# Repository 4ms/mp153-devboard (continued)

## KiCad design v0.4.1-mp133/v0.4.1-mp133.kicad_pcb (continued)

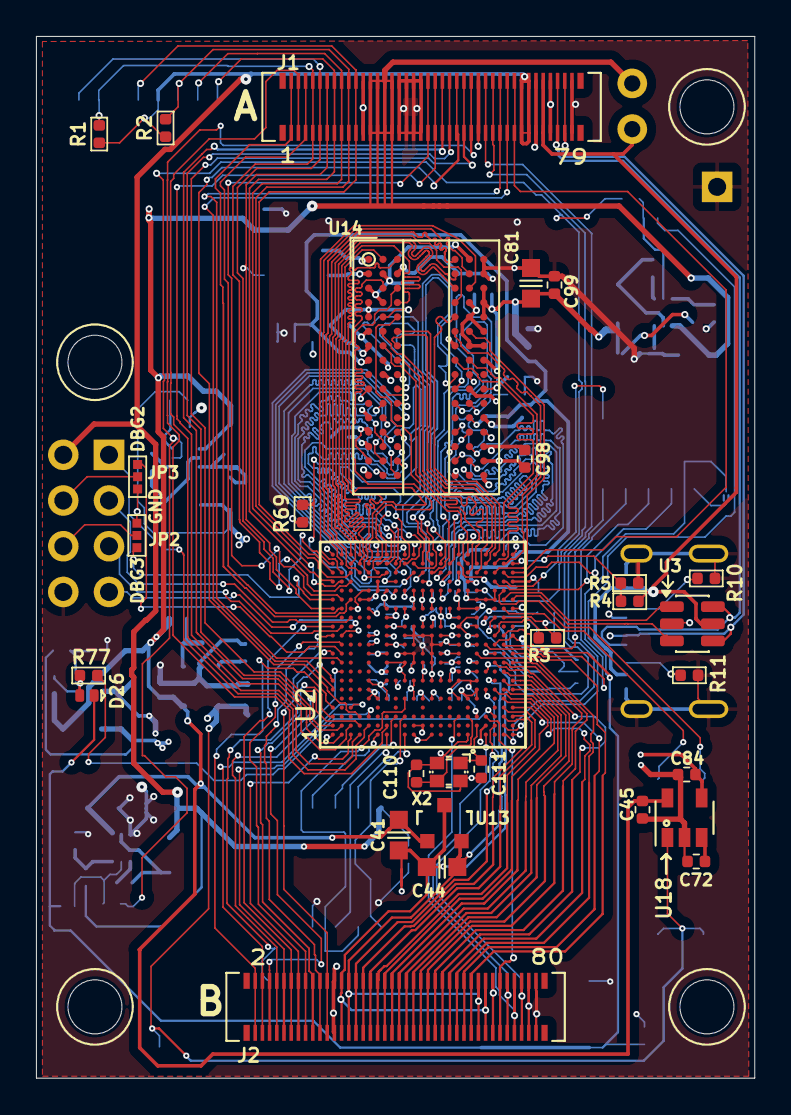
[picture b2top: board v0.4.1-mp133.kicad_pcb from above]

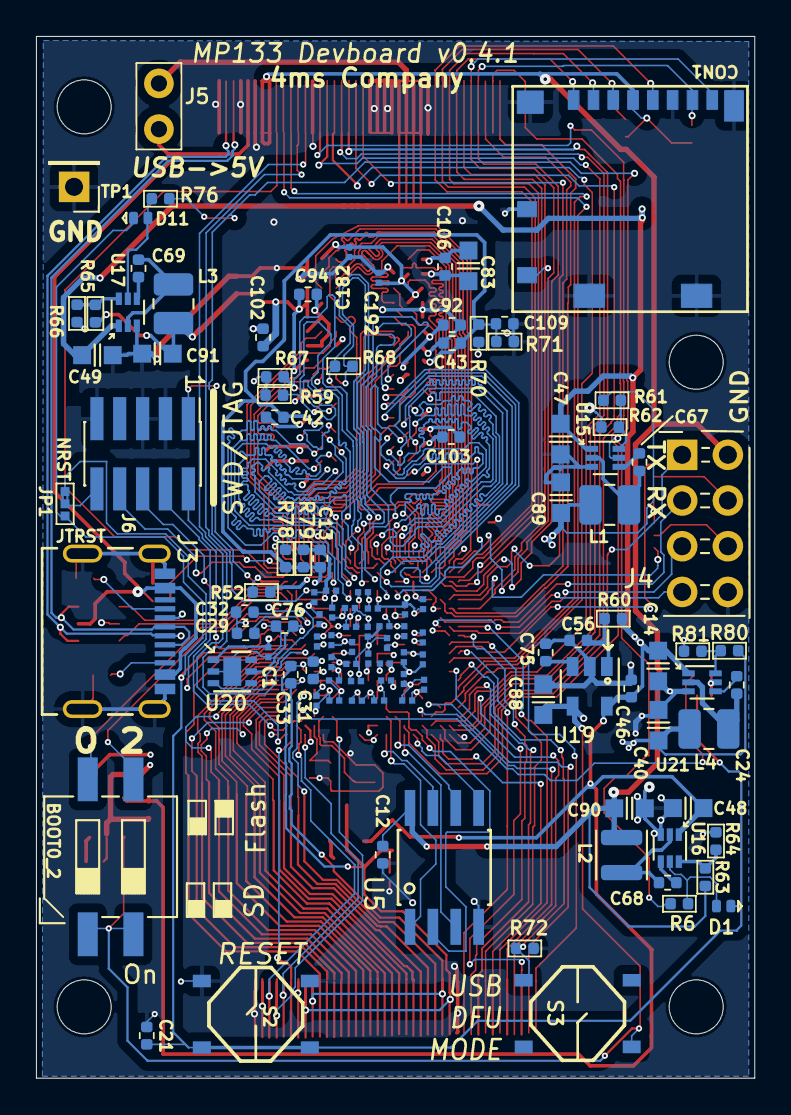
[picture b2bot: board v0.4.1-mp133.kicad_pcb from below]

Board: 4 copper layers, 39.9 x 57.9 mm, 148 parts (113 on the bottom side), 174 nets.

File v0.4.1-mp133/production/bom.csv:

Designator,Footprint,Quantity,Value,LCSC Part #
BOOT0_2,SW_DIP_SPSTx02_CTS_219-2MSTR,1,SW_DIP_x02_CTS_219-2MST,C2961978
"C1, C174, C176, C177, C182, C183, C185, C186, C187, C188, C189, C190, C191, C194, C195, C196, C197, C198, C199, C200, C201, C202, C203, C205, C207, C208, C209, C212, C213, C215",C_0201,30,1uF_0201_4V,C541330
"C102, C103, C106, C12, C21, C24, C42, C43, C67, C68, C69, C92, C94, C98, C99",C_0402,15,100nF_0402_16V,C1525
"C109, C13, C31, C33, C45, C46",C_0402,6,1uF_0402_25V,C52923
"C110, C111",C_0402,2,6.8pF_0402_25V,C1576
"C14, C41, C47, C48, C49",C_0603,5,2.2uF_0603_25V,C57895
"C175, C184, C192, C193, C204, C206, C211",C_0201,7,1nF_0201_4V,C505464
"C29, C32",C_0402,2,2.2uF_0402_6.3V,C12530
"C40, C88, C89, C90, C91",C_0603,5,22uF_0603_6.3V,C59461
"C44, C81, C83",C_0603,3,10uF_0603_10V,C19702
"C56, C72, C75",C_0402,3,100nF_0402_50V,C307331
"C76, C84",C_0402,2,4.7uF_0402_6.3V,C23733
CON1,CardSlot_MicroSD_Molex_104031-0811,1,microSDCon_SMT_104031-0811,C585350
"D1, D11, D26",DFN-1006-2,3,BAT54LP,C134410
"J1, J2",Connector-80pin-P0.4mm-W3.0mm,2,Pins_02x40_P0.4mm_W3.0mm_SMT,C19089237
J3,USB_C_Receptacle_Molex_2171790001,1,USB-C_Receptacle_Molex_2171790001,C2894899
J6,Pins_2x05_1.27mm_SMD,1,Pins_02x05_P1.27mm_SMT,C598540
"L1, L3, L4",1008,3,1uH_3.2A_2520,C435392
L2,L_Wuerth_MAPI-2510,1,4.7uH_1.7A_2510,C2047781
"R1, R2, R6, R61, R64, R66, R67, R69, R72, R76, R77, R80",R_0402,12,10k_0402,C60490
"R10, R11",R_0402,2,5.1k_0402,C105872
R3,R_0402,1,3k_0402,C137987
R4,R_0402,1,430k_0402,C163463
R5,R_0402,1,620k_0402,C137952
"R52, R59",R_0402,2,240?_0402,C114755
R60,R_0402,1,100k_0402,C60491
R62,R_0402,1,17.4k_0402,C327366
R63,R_0402,1,31.6k_0402,C276265
R65,R_0402,1,6.8k_0402,C93940
R68,R_0402,1,100?_0402,C106232
"R70, R71, R78, R79",R_0402,4,1k_0402,C106235
R81,R_0402,1,14.7k_0402,C138055
"S2, S3",Button_Tact_PTS526,2,SW_Push_PTS526 SM15 SMTR2 LFS,C2689521
U13,SOT23-3_PO132,1,NCP51460SN33,C233715 
U14,FBGA-96_Layout2x3x16_Body8x14_P0.8mm,1,DDR3L-RAM-4Gb_MT41K256M16TW,C253882
"U15, U16, U17, U21",SOT-563,4,AP6230xZ6,C1880992
"U18, U19",SOT-23-5,2,TAR5S33,C2762700
U2,TFBGA-320_11x11mm_P0.5,1,STM32MP135AAF3,C20033858 
U20,DFN-6-1EP_2x2mm_P0.65mm_EP1x1.6mm,1,AP2411SN,C2759889 
U3,SOT-23-6,1,USBLC6-2SC6,C2827654
U5,SOIC-8_5.28x4.9mm_Pitch1.27mm,1,NORFLASH_W25Q128JV,C113767
X2,Crystal_2.0x1.6mm_4pin,1,24MHz_9pF_2x1.6mm,C498196

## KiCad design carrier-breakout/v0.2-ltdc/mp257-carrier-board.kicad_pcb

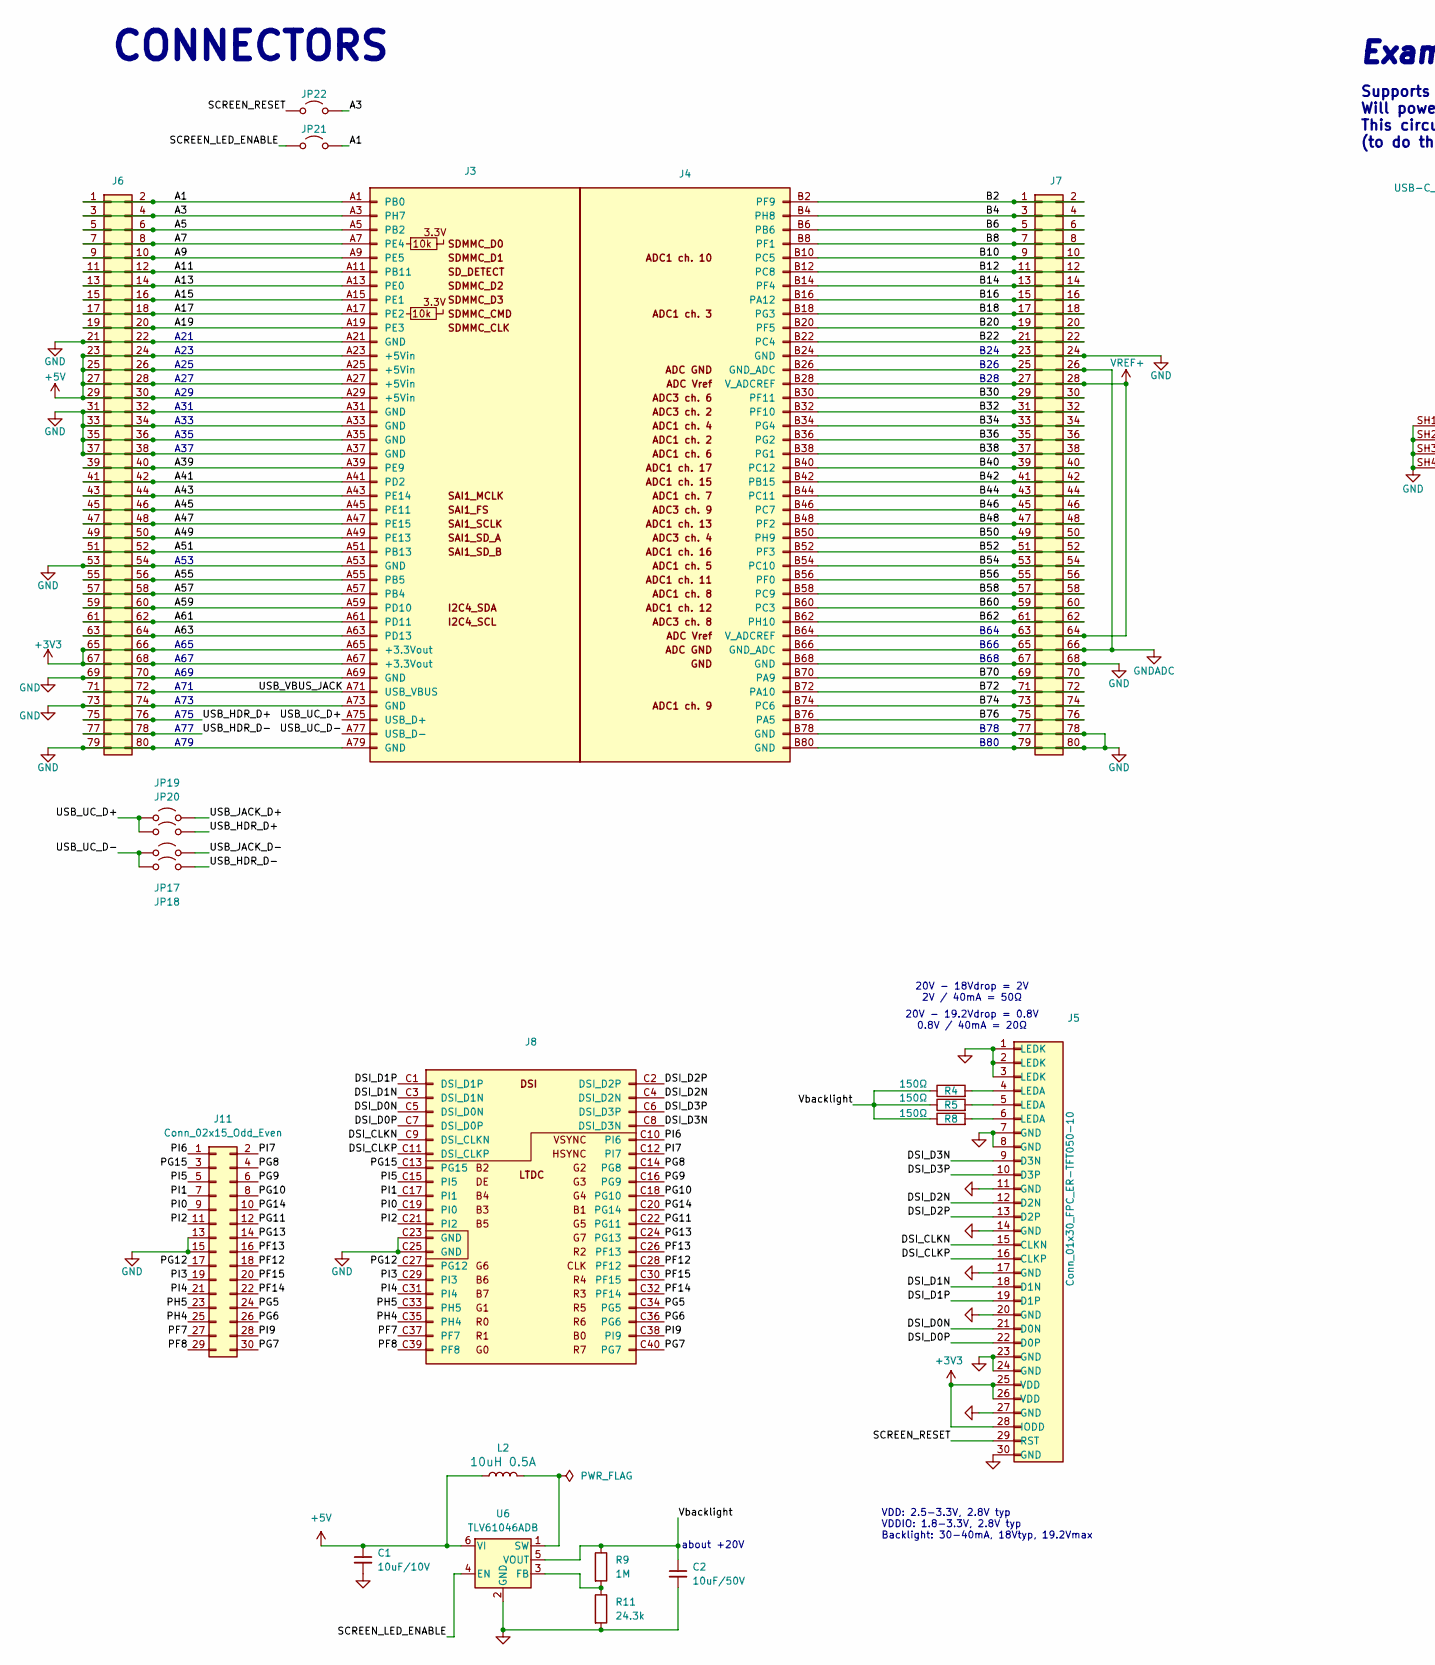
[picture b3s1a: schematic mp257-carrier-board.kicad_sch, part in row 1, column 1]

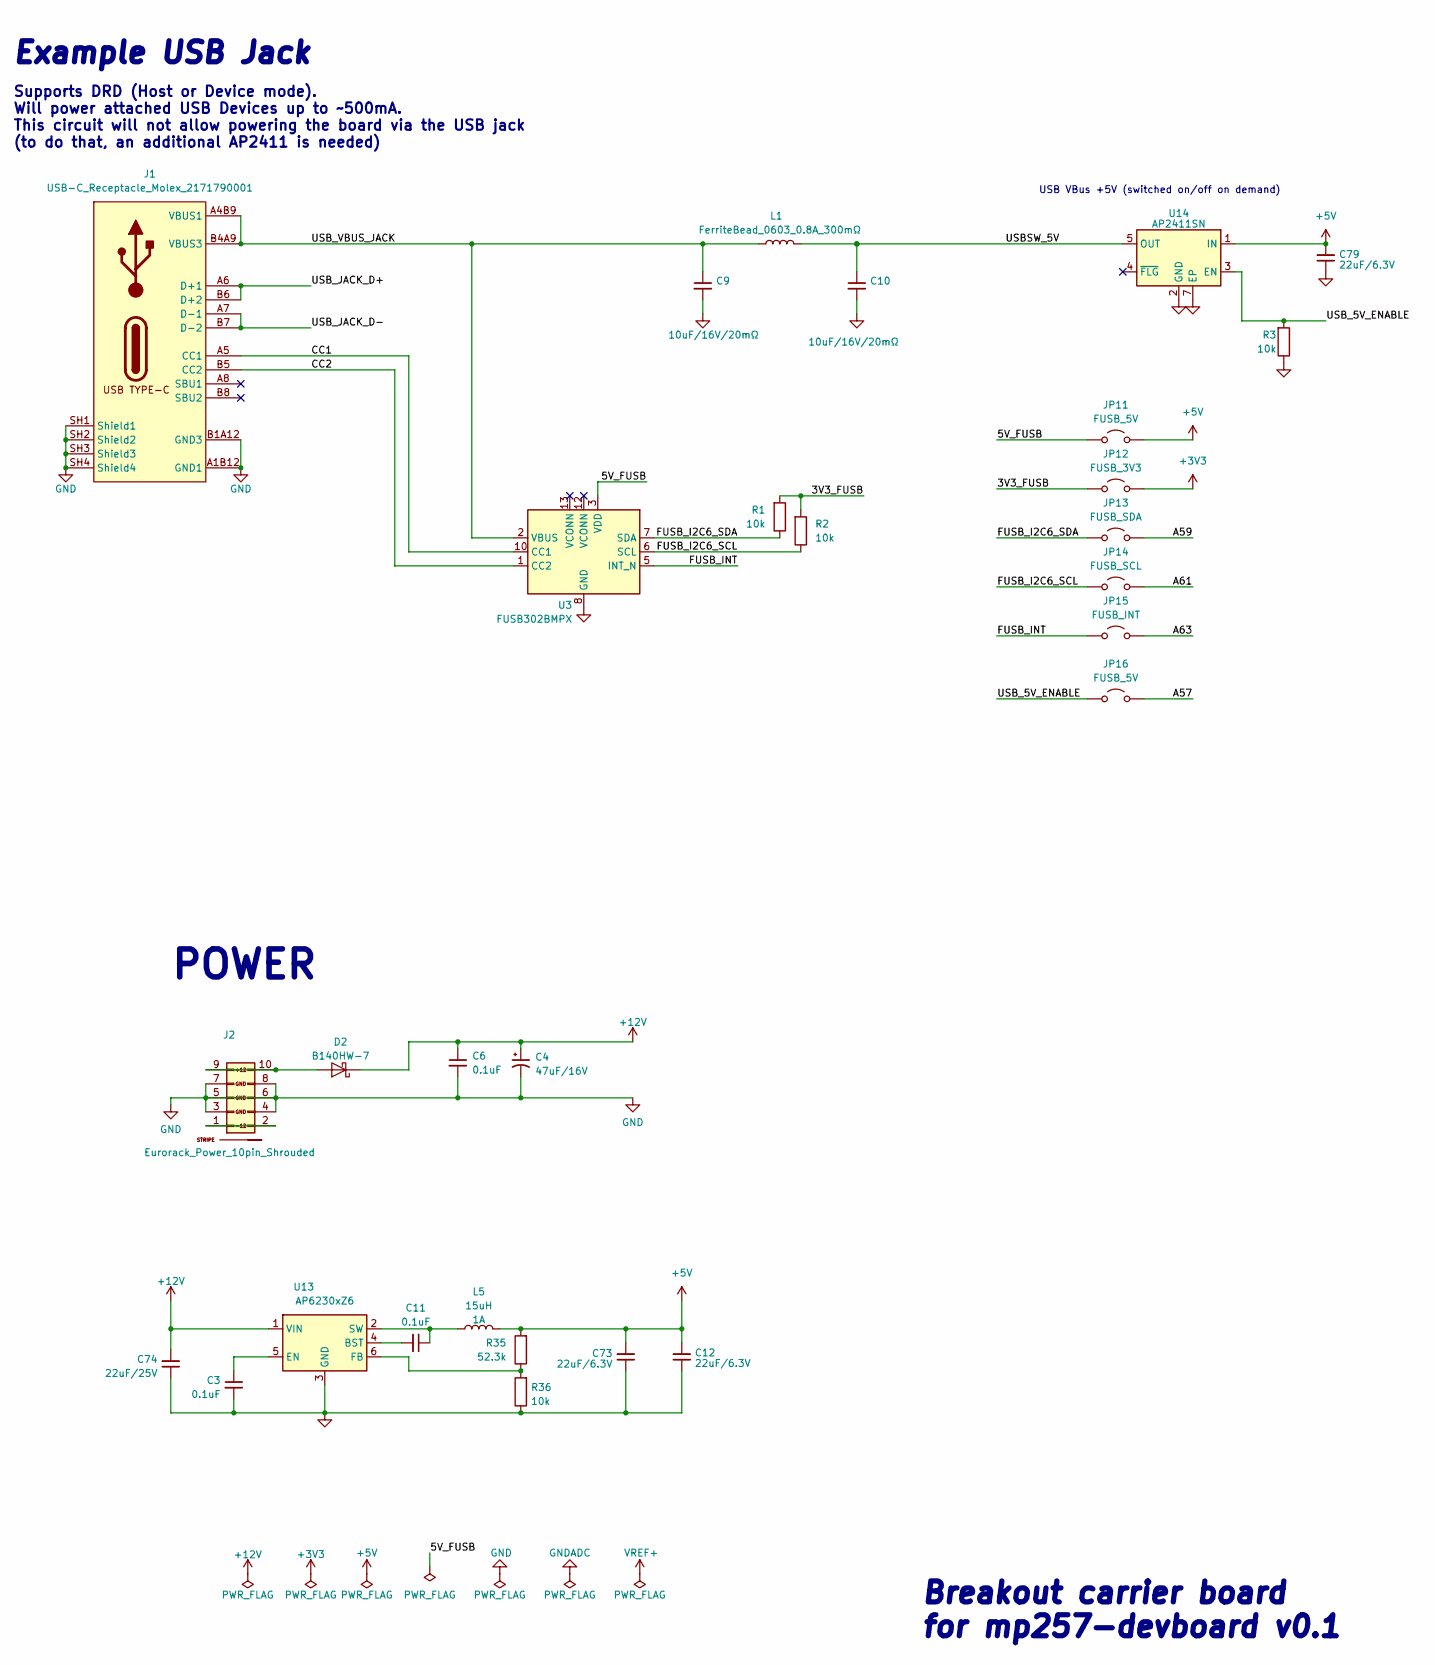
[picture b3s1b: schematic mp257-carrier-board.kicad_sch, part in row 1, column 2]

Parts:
C1: 10uF_0603_10V; C_0603; Part Number GRM188R61A106KE69D; JLCPCB ID C19702
C2: 10uF_1210_35V; C_1210; Part Number GMK325BJ106MN-T; JLCPCB ID C172721
C3, C11: 100nF_0402_50V; C_0402; Part Number GCM155R71C104KA55D; JLCPCB ID C1525
C4: 47uF_5x5.3_16V; CP_Elec_5x5.3; Part Number VES470M1CTR-0505; JLCPCB ID C134798
C6: 100nF_0603_16V; C_0603; Part Number 0603YC104KAT2A; JLCPCB ID C14663
C9, C10: 10uF_0805_16V_lowESR; C_0805; Part Number EMK212ABJ106KG-T; JLCPCB ID C190442
C12, C73, C79: 22uF_0603_6.3V; C_0603; Part Number GRM188R60J226MEA0J; JLCPCB ID C59461
C74: 22uF_0805_25V; C_1206; Part Number TMK316BBJ226ML-T; JLCPCB ID C12891
D2: B140HW-7; D_SOD-123; Part Number B140HW-7; JLCPCB ID C134429
J1: USB-C_Receptacle_Molex_2171790001; USB_C_Receptacle_Molex_2171790001; Part Number 217179-0001; JLCPCB ID C2894899
J2: Eurorack_Power_10pin_Shrouded; Pins_2x05_2.54mm_TH_EurorackPower_Shrouded; Part Number 61201021621
J3: mp153-devboard-sockets_A; Part Number DF40HC(3.0)-80DS-0.4V(51); JLCPCB ID C2858577
J4: mp153-devboard-sockets_B; Part Number DF40HC(3.0)-80DS-0.4V(51); JLCPCB ID C2858577
J5: Conn_01x30_FPC_ER-TFT050-10; FPC_30pin_FPC-05FB-30PH20
J6, J7: Pins_02x40_P2.54mm_TH; Pins_2x40_P2.54mm_TH
J8: mp153-devboard-sockets_C; Part Number DF40HC(3.0)-40DS-0.4V(51); JLCPCB ID C3651056
J11: Conn_02x15_Odd_Even; PinHeader_2x15_P2.54mm_Vertical
JP11, JP12, JP13, JP14, JP15, JP16, JP17, JP18, JP19, JP20, JP21, JP22: SolderJumper_2_Open; JUMPER_SMD_1x2_tiny
L1: FerriteBead_0603_0.8A_300mΩ; R_0603; Part Number MPZ1608S102ATA00; JLCPCB ID C76814
L2: 10uH_0805_0.5A; R_0805_2012Metric; Part Number MLZ2012N100L; JLCPCB ID C88182
L5: 15uH_1A_5040; COIL_5040; Part Number SRN5040TA-150M; JLCPCB ID C222950
R1, R2, R3, R36: 10k_0402; R_0402; Part Number RC0402FR-0710KL; JLCPCB ID C60490
R4, R5, R8: 150Ω_0603; R_0603; Part Number RC0603FR-07150RL; JLCPCB ID C114608
R9: 1M_0402; R_0402; Part Number RC0402FR-071ML; JLCPCB ID C138033
R11: 24.3k_0402; R_0402; Part Number RC0402FR-0724K3L; JLCPCB ID C276264
R35: 52.3k_0402; R_0402; Part Number RC0402FR-0752K3L; JLCPCB ID C276275
U3: FUSB302BMPX; WQFN-14-1EP_2.5x2.5mm_P0.5mm_EP1.45x1.45mm; Part Number FUSB302BMPX; JLCPCB ID C132291
U6: TLV61046ADB; SOT-23-6
U13: AP6230xZ6; SOT-563; Part Number AP62301Z6; JLCPCB ID C1880992
U14: AP2411SN; DFN-6-1EP_2x2mm_P0.65mm_EP1x1.6mm; Part Number AP2411SN-7; JLCPCB ID C2149815

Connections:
+3V3: J3.A65 (+3.3Vout), J3.A67 (+3.3Vout), J5.25 (VDD), J5.26 (VDD), J5.28 (IODD), J6.65, J6.66, J6.67, J6.68, JP12.2 (B)
+5V: C1.1, C12.2, C73.2, C79.2, J3.A23 (+5Vin), J3.A25 (+5Vin), J3.A27 (+5Vin), J3.A29 (+5Vin), J6.23, J6.24, J6.25, J6.26, J6.27, J6.28, J6.29, J6.30, JP11.2 (B), L2.1, L5.2, R35.2, U6.6 (VI), U14.1 (IN)
+12V: C4.1, C6.1, C74.2, D2.1 (K), U13.1 (VIN)
/3V3_FUSB: JP12.1 (A), R1.2, R2.2
/5V_FUSB: JP11.1 (A), U3.3 (VDD), U3.4 (VDD)
/A1: J3.A1 (PB0), J6.1, J6.2, JP21.2 (B)
/A3: J3.A3 (PH7), J6.3, J6.4, JP22.2 (B)
/A5: J3.A5 (PB2), J6.5, J6.6
/A7: J3.A7 (PE4), J6.7, J6.8
/A9: J3.A9 (PE5), J6.9, J6.10
/A11: J3.A11 (PB11), J6.11, J6.12
/A13: J3.A13 (PE0), J6.13, J6.14
/A15: J3.A15 (PE1), J6.15, J6.16
/A17: J3.A17 (PE2), J6.17, J6.18
/A19: J3.A19 (PE3), J6.19, J6.20
/A39: J3.A39 (PE9), J6.39, J6.40
/A41: J3.A41 (PD2), J6.41, J6.42
/A43: J3.A43 (PE14), J6.43, J6.44
/A45: J3.A45 (PE11), J6.45, J6.46
/A47: J3.A47 (PE15), J6.47, J6.48
/A49: J3.A49 (PE13), J6.49, J6.50
/A51: J3.A51 (PB13), J6.51, J6.52
/A55: J3.A55 (PB5), J6.55, J6.56
/A57: J3.A57 (PB4), J6.57, J6.58, JP16.2 (B)
/A59: J3.A59 (PD10), J6.59, J6.60, JP13.2 (B)
/A61: J3.A61 (PD11), J6.61, J6.62, JP14.2 (B)
/A63: J3.A63 (PD13), J6.63, J6.64, JP15.2 (B)
/B2: J4.B2 (PF9), J7.1, J7.2
/B4: J4.B4 (PH8), J7.3, J7.4
/B6: J4.B6, J7.5, J7.6
/B8: J4.B8 (PF1), J7.7, J7.8
/B10: J4.B10 (PC5), J7.9, J7.10
/B12: J4.B12 (PC8), J7.11, J7.12
/B14: J4.B14 (PF4), J7.13, J7.14
/B16: J4.B16 (PA12), J7.15, J7.16
/B18: J4.B18 (PG3), J7.17, J7.18
/B20: J4.B20 (PF5), J7.19, J7.20
/B22: J4.B22 (PC4), J7.21, J7.22
/B30: J4.B30 (PF11), J7.29, J7.30
/B32: J4.B32 (PF10), J7.31, J7.32
/B34: J4.B34 (PG4), J7.33, J7.34
/B36: J4.B36 (PG2), J7.35, J7.36
/B38: J4.B38 (PG1), J7.37, J7.38
/B40: J4.B40 (PC12), J7.39, J7.40
/B42: J4.B42 (PB15), J7.41, J7.42
/B44: J4.B44 (PC11), J7.43, J7.44
/B46: J4.B46 (PC7), J7.45, J7.46
/B48: J4.B48 (PF2), J7.47, J7.48
/B50: J4.B50 (PH9), J7.49, J7.50
/B52: J4.B52 (PF3), J7.51, J7.52
/B54: J4.B54 (PC10), J7.53, J7.54
/B56: J4.B56 (PF0), J7.55, J7.56
/B58: J4.B58 (PC9), J7.57, J7.58
/B60: J4.B60 (PC3), J7.59, J7.60
/B62: J4.B62 (PH10), J7.61, J7.62
/B70: J4.B70 (PA9), J7.69, J7.70
/B72: J4.B72 (PA10), J7.71, J7.72
/B74: J4.B74 (PC6), J7.73, J7.74
/B76: J4.B76 (PA5), J7.75, J7.76
/CC1: J1.A5 (CC1), U3.10 (CC1), U3.11 (CC1)
/CC2: J1.B5 (CC2), U3.1 (CC2), U3.14 (CC2)
/DSI_CLKN: J5.15 (CLKN), J8.C9 (DSI_CLKN)
/DSI_CLKP: J5.16 (CLKP), J8.C11 (DSI_CLKP)
/DSI_D0N: J5.21 (D0N), J8.C5 (DSI_D0N)
/DSI_D0P: J5.22 (D0P), J8.C7 (DSI_D0P)
/DSI_D1N: J5.18 (D1N), J8.C3 (DSI_D1N)
/DSI_D1P: J5.19 (D1P), J8.C1 (DSI_D1P)
/DSI_D2N: J5.12 (D2N), J8.C4 (DSI_D2N)
/DSI_D2P: J5.13 (D2P), J8.C2 (DSI_D2P)
/DSI_D3N: J5.9 (D3N), J8.C8 (DSI_D3N)
/DSI_D3P: J5.10 (D3P), J8.C6 (DSI_D3P)
/FUSB_I2C6_SCL: JP14.1 (A), R2.1, U3.6 (SCL)
/FUSB_I2C6_SDA: JP13.1 (A), R1.1, U3.7 (SDA)
/FUSB_INT: JP15.1 (A), U3.5 (INT_N)
/PF7: J8.C37 (PF7), J11.27
/PF8: J8.C39 (PF8), J11.29
/PF12: J8.C28 (PF12), J11.18
/PF13: J8.C26 (PF13), J11.16
/PF14: J8.C32 (PF14), J11.22
/PF15: J8.C30 (PF15), J11.20
/PG5: J8.C34 (PG5), J11.24
/PG6: J8.C36 (PG6), J11.26
/PG7: J8.C40 (PG7), J11.30
/PG8: J8.C14 (PG8), J11.4
/PG9: J8.C16 (PG9), J11.6
/PG10: J8.C18 (PG10), J11.8
/PG11: J8.C22 (PG11), J11.12
/PG12: J8.C27 (PG12), J11.17
/PG13: J8.C24 (PG13), J11.14
/PG14: J8.C20 (PG14), J11.10
/PG15: J8.C13 (PG15), J11.3
/PH4: J8.C35 (PH4), J11.25
/PH5: J8.C33 (PH5), J11.23
/PI0: J8.C19 (PI0), J11.9
/PI1: J8.C17 (PI1), J11.7
/PI2: J8.C21 (PI2), J11.11
/PI3: J8.C29 (PI3), J11.19
/PI4: J8.C31 (PI4), J11.21
/PI5: J8.C15 (PI5), J11.5
/PI6: J8.C10 (PI6), J11.1
/PI7: J8.C12 (PI7), J11.2
/PI9: J8.C38 (PI9), J11.28
/SCREEN_LED_ENABLE: JP21.1 (A), U6.4 (EN)
/SCREEN_RESET: J5.29 (RST), JP22.1 (A)
/USBSW_5V: C10.1, L1.1, U14.5 (OUT)
/USB_5V_ENABLE: JP16.1 (A), R3.2, U14.3 (EN)
/USB_HDR_D+: J6.75, J6.76, JP20.2 (B)
/USB_HDR_D-: J6.77, J6.78, JP18.2 (B)
/USB_JACK_D+: J1.A6 (D+1), J1.B6 (D+2), JP19.2 (B)
/USB_JACK_D-: J1.A7 (D-1), J1.B7 (D-2), JP17.2 (B)
/USB_UC_D+: J3.A75 (USB_D+), JP19.1 (A), JP20.1 (A)
/USB_UC_D-: J3.A77 (USB_D-), JP17.1 (A), JP18.1 (A)
/USB_VBUS_JACK: C9.1, J1.A4B9 (VBUS1), J1.B4A9 (VBUS3), J3.A71 (USB_VBUS), J6.71, J6.72, L1.2, U3.2 (VBUS)
/Vbacklight: C2.1, R4.1, R5.1, R8.1, R9.1, U6.5 (VOUT)
GND: C1.2, C2.2, C3.2, C4.2, C6.2, C9.2, C10.2, C12.1, C73.1, C74.1, C79.1, J1.A1B12 (GND1), J1.B1A12 (GND3), J1.SH1 (Shield1), J1.SH2 (Shield2), J1.SH3 (Shield3), J1.SH4 (Shield4), J2.3 (GND), J2.4 (GND), J2.5 (GND), J2.6 (GND), J2.7 (GND), J2.8 (GND), J3.A21 (GND), J3.A31 (GND), J3.A33 (GND), J3.A35 (GND), J3.A37 (GND), J3.A53 (GND), J3.A69 (GND), J3.A73 (GND), J3.A79 (GND), J4.B24 (GND), J4.B68 (GND), J4.B78 (GND), J4.B80 (GND), J5.1 (LEDK), J5.2 (LEDK), J5.3 (LEDK), J5.7 (GND), J5.8 (GND), J5.11 (GND), J5.14 (GND), J5.17 (GND), J5.20 (GND), J5.23 (GND), J5.24 (GND), J5.27 (GND), J5.30 (GND), J6.21, J6.22, J6.31, J6.32, J6.33, J6.34, J6.35, J6.36, J6.37, J6.38, J6.53, J6.54, J6.69, J6.70, J6.73, J6.74, J6.79, J6.80, J7.23, J7.24, J7.67, J7.68, J7.77, J7.78, J7.79, J7.80, J8.C23 (GND), J8.C25 (GND), J11.13, J11.15, R3.1, R11.2, R36.1, U3.8 (GND), U3.9 (GND), U3.15 (GND), U6.2 (GND), U13.3 (GND), U14.2 (GND), U14.7 (EP)
GNDADC: J4.B26 (GND_ADC), J4.B66 (GND_ADC), J7.25, J7.26, J7.65, J7.66
unnamed: D2.2 (A), J2.9 (+12V), J2.10 (+12V)
unnamed: J2.1 (-12V), J2.2 (-12V)
unnamed: J5.4 (LEDA), R4.2
unnamed: J5.5 (LEDA), R5.2
unnamed: J5.6 (LEDA), R8.2
unnamed: R9.2, R11.1, U6.3 (FB)
unnamed: L2.2, U6.1 (SW)
unnamed: C11.2, U13.4 (BST)
unnamed: C3.1, U13.5 (EN)
unnamed: R35.1, R36.2, U13.6 (FB)
unnamed: C11.1, L5.1, U13.2 (SW)
VREF+: J4.B28 (V_ADCREF), J4.B64 (V_ADCREF), J7.27, J7.28, J7.63, J7.64

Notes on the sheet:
A73
VDD: 2.5-3.3V, 2.8V typ VDDIO: 1.8-3.3V, 2.8V typ Backlight: 30-40mA, 18Vtyp, 19.2Vmax
A37
A33
A77
POWER
B80
A65
about +20V
B64
A25
A71
A69
B28
B24
CONNECTORS
B26
B68
Supports DRD (Host or Device mode). Will power attached USB Devices up to ~500mA. This circuit will not allow powering the board via the USB jack (to do that, an additional AP2411 is needed)
A79
A75
Example USB Jack
A67
A31
A29
20V - 18Vdrop = 2V 2V / 40mA = 50Ω
A21
Breakout carrier board for mp257-devboard v0.1
B78
B66
A35
USB VBus +5V (switched on/off on demand)
A53
A23
A27
20V - 19.2Vdrop = 0.8V 0.8V / 40mA = 20Ω

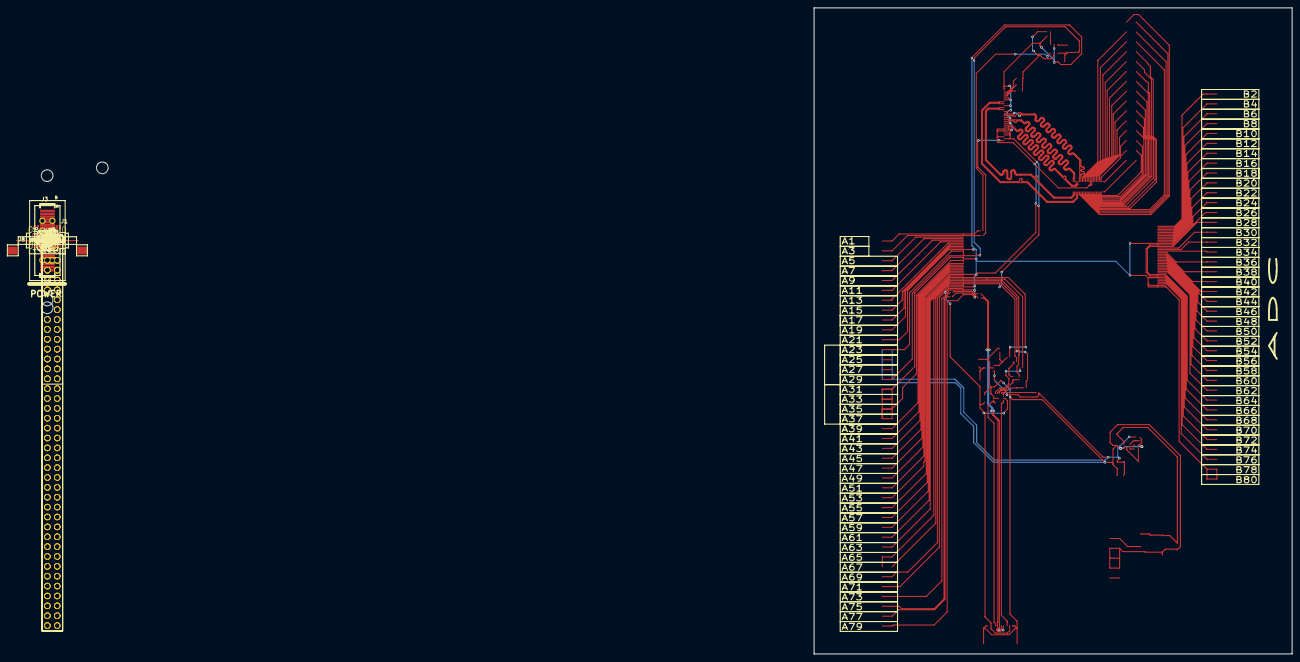
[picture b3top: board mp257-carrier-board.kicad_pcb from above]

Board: 2 copper layers, 123.0 x 166.2 mm, 51 parts (0 on the bottom side), 128 nets.

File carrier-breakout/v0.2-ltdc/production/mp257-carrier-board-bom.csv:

Designator,Footprint,Quantity,Value,LCSC Part #
"J3,J4","4ms_Connector_Card:mp153-devboard-sockets_A,4ms_Connector_Card:mp153-devboard-sockets_B","2","","C2858577"
"C3,C11","4ms_Capacitor:C_0402","2","100nF_0402_50V","C1525"
"C1","4ms_Capacitor:C_0603","1","10uF_0603_10V","C19702"
"C6","4ms_Capacitor:C_0603","1","100nF_0603_16V","C14663"
"C12,C73,C79","4ms_Capacitor:C_0603","3","22uF_0603_6.3V","C59461"
"C9,C10","4ms_Capacitor:C_0805","2","10uF_0805_16V_lowESR","C190442"
"C74","4ms_Capacitor:C_1206","1","22uF_0805_25V","C12891"
"C2","4ms_Capacitor:C_1210","1","10uF_1210_35V","C172721"
"C4","4ms_Capacitor:CP_Elec_5x5.3","1","47uF_5x5.3_16V","C134798"
"J5","4ms_Connector:FPC_30pin_FPC-05FB-30PH20","1","Conn_01x30_FPC_ER-TFT050-10","C2856833"
"J2","4ms_Connector:Pins_2x05_2.54mm_TH_EurorackPower_Shrouded","1","Eurorack_Power_10pin_Shrouded",""
"J6,J7","4ms_Connector:Pins_2x40_P2.54mm_TH","2","Pins_02x40_P2.54mm_TH",""
"J1","4ms_Connector:USB_C_Receptacle_Molex_2171790001","1","USB-C_Receptacle_Molex_2171790001","C2894899"
"J8","4ms_Connector_Card:mp153-devboard-sockets_C","1","~","C3651056"
"D2","4ms_Diode:D_SOD-123","1","B140HW-7","C134429"
"L5","4ms_Inductor:COIL_5040","1","15uH_1A_5040","C222950"
"U14","4ms_Package_QFP:DFN-6-1EP_2x2mm_P0.65mm_EP1x1.6mm","1","AP2411SN","C2149815"
"U13","4ms_Package_SOT:SOT-563","1","AP6230xZ6","C1880992"
"R1,R2,R3,R36","4ms_Resistor:R_0402","4","10k_0402","C60490"
"R9","4ms_Resistor:R_0402","1","1M_0402","C138033"
"R11","4ms_Resistor:R_0402","1","24.3k_0402","C276264"
"R35","4ms_Resistor:R_0402","1","52.3k_0402","C276275"
"L1","4ms_Resistor:R_0603","1","FerriteBead_0603_0.8A_300mΩ","C76814"
"R4,R5,R8","4ms_Resistor:R_0603","3","150Ω_0603","C114608"
"L2","4ms_Resistor:R_0805_2012Metric","1","10uH_0805_0.5A","C88182"
"JP11,JP12,JP13,JP14,JP15,JP16,JP17,JP18,JP19,JP20,JP21,JP22","4ms_SolderJumper:JUMPER_SMD_1x2_tiny","12","SolderJumper_2_Open",""
"J11","Connector_PinHeader_2.54mm:PinHeader_2x15_P2.54mm_Vertical","1","Conn_02x15_Odd_Even",""
"U3","Package_DFN_QFN:WQFN-14-1EP_2.5x2.5mm_P0.5mm_EP1.45x1.45mm","1","FUSB302BMPX","C132291"
"U6","Package_TO_SOT_SMD:SOT-23-6","1","TLV61046ADB","C464815"
